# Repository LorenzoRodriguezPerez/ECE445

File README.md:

# ECE445
# Autonomous Sailboat Project - Team 2
Used STM32duino library and other sensor/module specific libraries. All final used code visible in "finalCode."

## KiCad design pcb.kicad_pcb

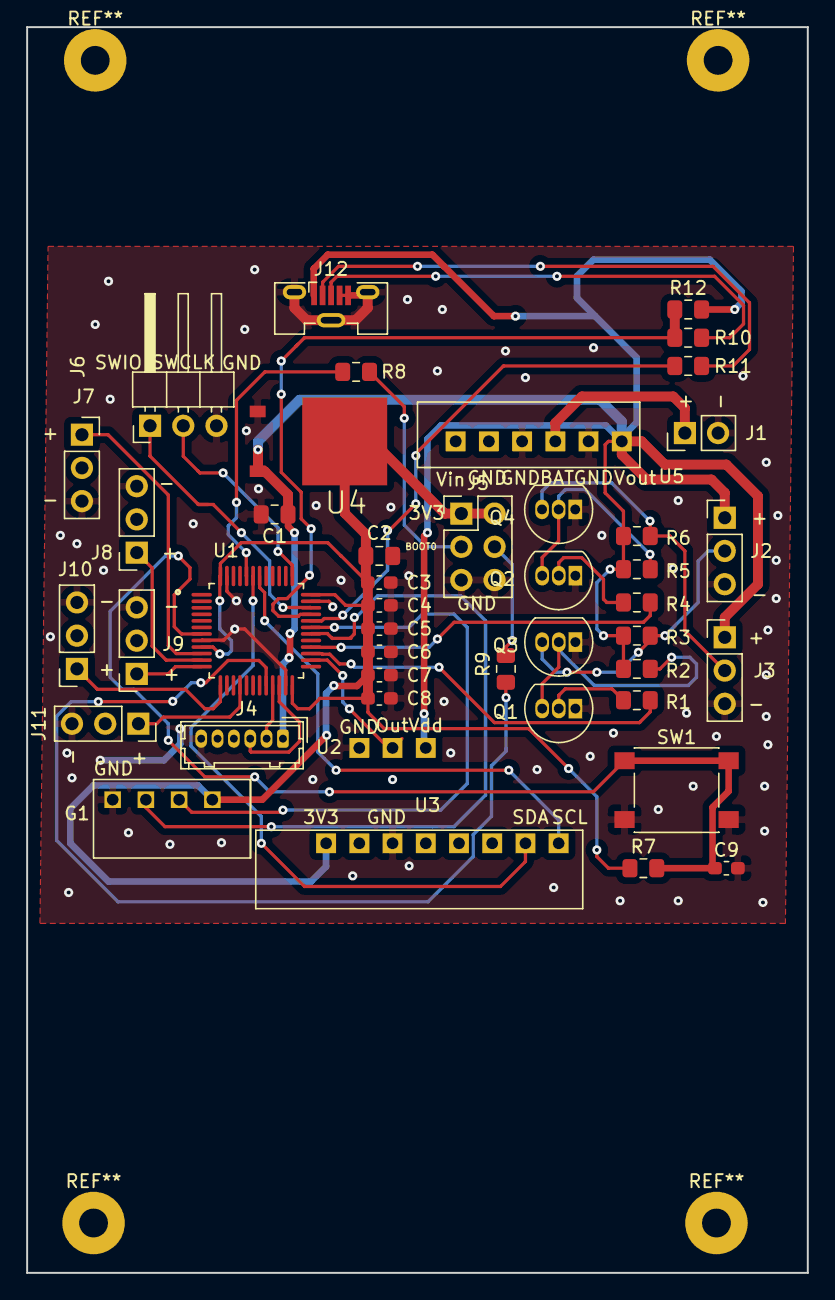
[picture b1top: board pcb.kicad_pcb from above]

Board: 2 copper layers, 59.7 x 95.2 mm, 44 parts (0 on the bottom side), 35 nets.

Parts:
C1, C2: 10uF; C_0805_2012Metric_Pad1.15x1.40mm_HandSolder
C3: 4.7uF; C_0603_1608Metric_Pad1.05x0.95mm_HandSolder
C4, C5, C6, C7, C8, C9: 100nF; C_0603_1608Metric_Pad1.05x0.95mm_HandSolder
G1: GPS_NEO_6M_module
J1: Conn_01x02; PinHeader_1x02_P2.54mm_Vertical
J2, J3: Conn_01x03; PinHeader_1x03_P2.54mm_Vertical
J4: Conn_01x06; Hirose_DF13-06P-1.25DSA_1x06_P1.25mm_Vertical
J5: Conn_02x03; PinHeader_2x03_P2.54mm_Vertical
J6: Conn_01x03-Connector_Generic; PinHeader_1x03_P2.54mm_Horizontal
J7, J8, J9, J10, J11: Conn_01x03-Connector_Generic; PinSocket_1x03_P2.54mm_Vertical
J12: USB_B_Micro; USB_Micro-B_Molex-105133-0031
Q1, Q2, Q3, Q4: 2N3904; TO-92_Inline
R1, R2, R4, R5, R12: 4.7K; R_0805_2012Metric_Pad1.15x1.40mm_HandSolder
R3, R6: 1K; R_0805_2012Metric_Pad1.15x1.40mm_HandSolder
R7: 10K; R_0805_2012Metric_Pad1.15x1.40mm_HandSolder
R8, R9: 100K; R_0805_2012Metric_Pad1.15x1.40mm_HandSolder
R10, R11: 20R; R_0805_2012Metric_Pad1.15x1.40mm_HandSolder
SW1: SW_Push; SW_SPST_PTS645
U1: STM32F103C8T6; QFP50P900X900X160-48N
U2: Shaft_encoder; shaft_encoder
U3: compass_accelerometer
U4: LM1117-3.3; TO228P970X238-3N
U5: 3v7_to_5V_boost

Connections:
+3V3: C2.1, C3.1, C4.1, C5.1, C6.1, C7.1, C8.1, G1.1, J5.1, J5.2, R7.1, U1.9, U1.24, U1.36, U1.48, U3.1, U4.2
+3V8: J1.1, U5.4
+5V: C1.1, J2.1, J3.1, J4.1, J12.1, R2.1, R3.1, R5.1, R6.1, R12.2, U2.1, U4.3, U5.6
BOOT0: R8.1, U1.44
BOOT1: R9.2, U1.20
GND: C1.2, C2.2, C3.2, C4.2, C5.2, C6.2, C7.2, C8.2, C9.2, G1.4, J1.2, J2.3, J3.3, J4.6, J5.5, J5.6, J6.3, J7.3, J8.3, J9.3, J10.3, J11.3, J12.4, J12.5, J12.6, Q1.1, Q2.1, Q3.1, Q4.1, SW1.2, U1.8, U1.23, U1.35, U1.47, U2.3, U3.7, U4.1, U5.3, U5.5
NRST: C9.1, R7.2, SW1.1, U1.7
unnamed: J2.2, Q3.3, R3.2
unnamed: J3.2, Q4.3, R6.2
unnamed: J5.3, R8.2
unnamed: J5.4, R9.1
unnamed: J12.2, R11.1
unnamed: J12.3, R10.1
unnamed: Q1.2, R1.1
unnamed: Q1.3, Q3.2, R2.2
unnamed: Q2.2, R4.1
unnamed: Q2.3, Q4.2, R5.2
PA0: J7.1, U1.10
PA1: J8.1, U1.11
PA2: J9.1, U1.12
PA3: J10.1, U1.13
PA6: J11.1, U1.16
PA9: G1.3, U1.30
PA10: G1.2, U1.31
PA11: R11.2, U1.32
PA12: R10.2, R12.1, U1.33
PA13: J6.1, U1.34
PA14: J6.2, U1.37
PB6: U1.42, U3.2
PB7: U1.43, U3.3
PB13: U1.26, U2.2
PB14: R1.2, U1.27
PB15: R4.2, U1.28
RX: J4.2, U1.21
TX: J4.3, U1.22

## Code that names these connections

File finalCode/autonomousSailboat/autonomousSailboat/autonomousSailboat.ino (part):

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const int telePeriod = 1000;

/* DEBUG -> UNPLUG CHANNELS 5 AND 6, CONNECT CHANNEL 5 TO RX OF CONVERTER */
//HardwareSerial debugSerial(PA3,PA2);

/* GPS VARIABLES */
TinyGPSPlus gps;
HardwareSerial gpsSerial(PA10, PA9);
static double _lat,_lng, base_lat, base_lng;
static float _course, _knots, _mph;

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/* CALIBRATION OF ECOMPASS */
unsigned long calibrationTime = 15000; //in ms

/* Setup pointers to eCompass module PB6 (SCL), PB7 (SDA) -> DONE IN WIRE.BEGIN() */
LSM303 compass;
LSM303::vector<int16_t> running_min = {32767,32767,32767}, running_max = {-32768,-32768,-32768};

/* RECEIVER CHANNEL ASSIGNMENTS 
 *  J7 = PA0, J8 PA1, J9 PA2, J10 PA3, J11 PA6
 *  CHANNEL 1: RIGHT JOY L/R -> Winch Control
 *  CHANNEL 2: RIGHT JOY U/D -> N/A
 *  CHANNEL 3: LEFT JOY U/D -> Rudder Control
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 *  CHANNEL 6: SWD -> 0->1: Set New Base Position
*/

#define CH1 PA0
#define CH3 PA1
#define CH5 PA2
#define CH6 PA3
//#define DEBUG PA6

// J2 PB14, J3 PB15
#define WINCH_SERVO PB14
#define RUDDER_SERVO PB15

/* ROTARY ENCODER SETUP */
#define WINDVANE_W PB13 
#define WINDVANE_G PA11
RotaryEncoder *encoder = nullptr;


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  attachInterrupt(digitalPinToInterrupt(CH6),ISR_BASE,CHANGE);

  /* ROTARY ENCODER SETUP */
  // WHITE = PB13, GREEN = PB12
  // use TWO03 mode when PIN_IN1, PIN_IN2 signals are both LOW or HIGH in latch position.
  encoder = new RotaryEncoder(WINDVANE_W, WINDVANE_G, RotaryEncoder::LatchMode::TWO03);
  attachInterrupt(digitalPinToInterrupt(WINDVANE_W), checkPosition, CHANGE);
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
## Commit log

2022-02-18 trying commits work out
2022-02-18 triying second commit
2022-02-18 Added led to schematic
2022-02-18 added microcontroller to schematic
2022-02-19 added correct MCU footprint and symbol
2022-02-20 created footprints and symbols for gps, compass and encoder
2022-02-21 added 3V7 to 3V3 convertor
2022-02-21 finished power supply
2022-02-22 changed 3v3 regulator
2022-02-24 changed 3v3 symbol
2022-02-24 I do not remember what I changed
2022-02-27 even more changes
2022-02-28 started layout
2022-03-01 evan recommmendations
2022-03-06 made changes into pcb, added python code
2022-03-06 added mounting holes
2022-03-06 drawings math model
2022-03-08 final changes to PCB
2022-03-10 broken simulation code
2022-03-10 handing off to lorenzo
2022-03-22 pcb final changes
2022-03-30 second round pcb
2022-05-05 Add files via upload
    Added ground control system code.
